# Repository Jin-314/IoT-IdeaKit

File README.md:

# Turtle Pico - Making electronics work easier and more widely

The Turtle Pico Board which looks like a turtle, uses connectors on the board for easy connection to components. The board is equipped with Raspberry Pi Pico W, and programming is easy with Micropython.

When you want to build something, just buy the components and plug them into this board! That's all there is to wiring. Then all you have to do is write the programming.

Don't know how to program? Don't worry. You can find some programming examples in the official repository.

## Specific & Environment build

Please see the specifications for a summary of each use.

The specifications are available in Japanese and English, so you can check them in the language of your choice.

[English](board/main/specific/specific_en.pdf)

[Japanese](board/main/specific/specific_jp.pdf)

## Case

Turtle Pico Package is available in [**board/main/Case**](https://github.com/Jin-Neuron/Turtle-Pico/tree/master/board/main/Case).

## Purchase your board

Turtle Pico boards can currently only be purchased from [PCBWay's Shared Project Page](https://www.pcbway.com/project/shareproject/Turtle_Pico_Board_c183b11f.html). Once officially released, we plan to make it available for purchase at various online stores. 

## License

This repository includes multiple components with different licenses.

Please reffer to [LICENSE File](License.txt).

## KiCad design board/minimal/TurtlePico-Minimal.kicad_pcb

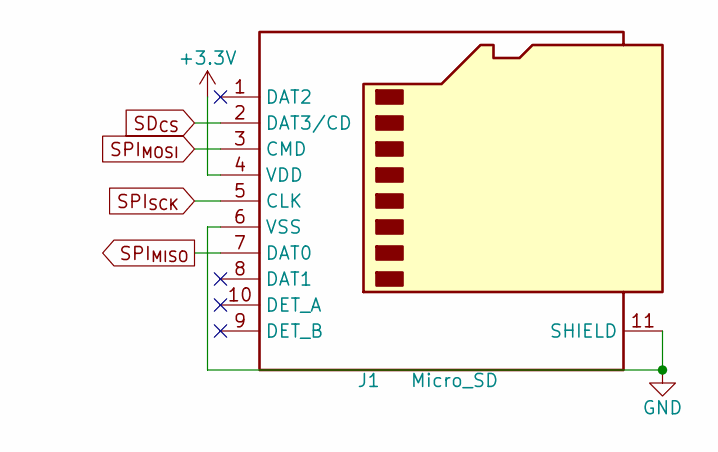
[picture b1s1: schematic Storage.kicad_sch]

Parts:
J1: Micro_SD; microSD_HC_Hirose_DM3D-SF; Manufacturer_Part_Number DM3AT-SF-PEJM5; Mouser Part Number 798-DM3AT-SF-PEJM5

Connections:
+3.3V: J1.4 (VDD); also elsewhere on the board
GND: J1.6 (VSS), J1.11 (SHIELD); also elsewhere on the board
SD_{CS}: J1.2 (DAT3/CD); also elsewhere on the board
SPI_{MISO}: J1.7 (DAT0); also elsewhere on the board
SPI_{MOSI}: J1.3 (CMD); also elsewhere on the board
SPI_{SCK}: J1.5 (CLK); also elsewhere on the board

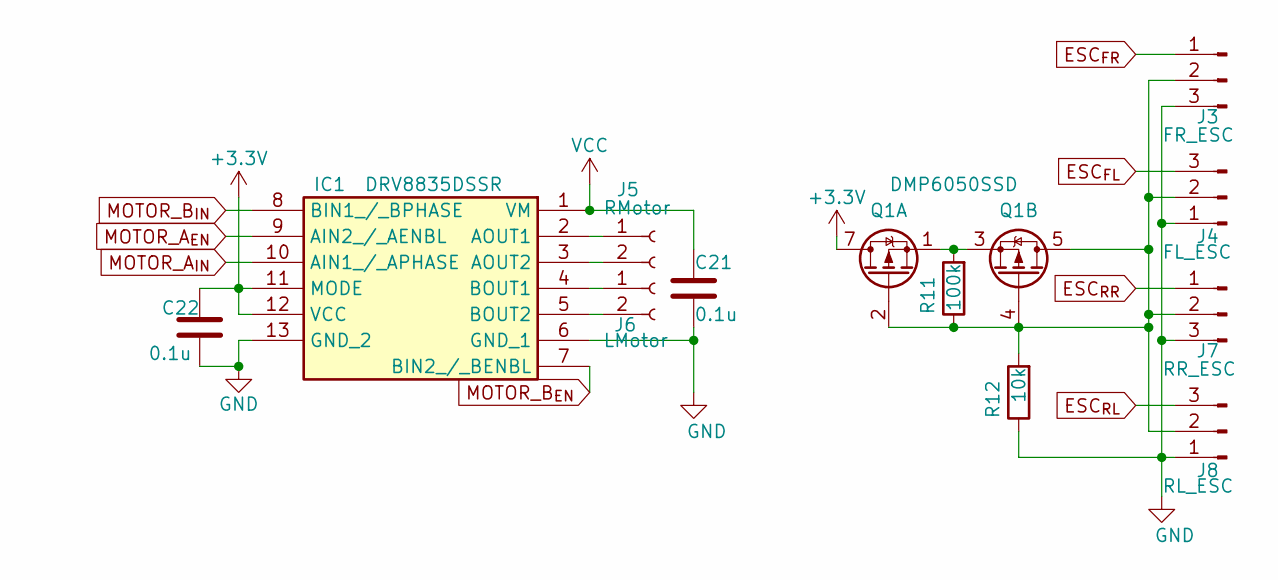
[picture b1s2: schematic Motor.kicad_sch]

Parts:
C21, C22: 0.1u; C_0201_0603Metric; Manufacturer_Part_Number GCM188R71C104KA37J; Mouser Part Number 81-GCM188R71C104KA7J
IC1: DRV8835DSSR; WSON-12-1EP_3x2mm_P0.5mm_EP1x2.65_ThermalVias; Mouser Part Number 595-DRV8835DSSR
J3: FR_ESC; PinHeader_1x03_P2.54mm_Horizontal
J4: FL_ESC; PinHeader_1x03_P2.54mm_Horizontal
J5: RMotor; PinSocket_1x02_P2.54mm_Vertical
J6: LMotor; PinSocket_1x02_P2.54mm_Vertical
J7: RR_ESC; PinHeader_1x03_P2.54mm_Horizontal
J8: RL_ESC; PinHeader_1x03_P2.54mm_Horizontal
Q1: DMP6050SSD; SOIC-8_3.9x4.9mm_P1.27mm
R11: 100k; R_0603_1608Metric; Manufacturer_Part_Number RN73H1JTTD5102F100; Mouser Part Number 660-RN73H1JT5102F100
R12: 10k; R_0603_1608Metric; Manufacturer_Part_Number RN73H1JTTD5102F100; Mouser Part Number 660-RN73H1JT5102F100

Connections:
+3.3V: C22.1, IC1.11 (MODE), IC1.12 (VCC), Q1.7 (D1), Q1.8 (D1); also elsewhere on the board
ESC_{FL}: J4.3; also elsewhere on the board
ESC_{FR}: J3.1; also elsewhere on the board
ESC_{RL}: J8.3; also elsewhere on the board
ESC_{RR}: J7.1; also elsewhere on the board
GND: C21.2, C22.2, IC1.6 (GND_1), IC1.13 (GND_2), J3.3, J4.1, J7.3, J8.1, R12.1; also elsewhere on the board
MOTOR_A_{EN}: IC1.9 (AIN2_/_AENBL); also elsewhere on the board
MOTOR_A_{IN}: IC1.10 (AIN1_/_APHASE); also elsewhere on the board
MOTOR_B_{EN}: IC1.7 (BIN2_/_BENBL); also elsewhere on the board
MOTOR_B_{IN}: IC1.8 (BIN1_/_BPHASE); also elsewhere on the board
unnamed: IC1.2 (AOUT1), J5.1
unnamed: IC1.3 (AOUT2), J5.2
unnamed: IC1.4 (BOUT1), J6.1
unnamed: IC1.5 (BOUT2), J6.2
unnamed: J3.2, J4.2, J7.2, J8.2, Q1.2 (G1), Q1.4 (G2), Q1.5 (D2), Q1.6 (D2), R11.1, R12.2
unnamed: Q1.1 (S1), Q1.3 (S2), R11.2
VCC: C21.1, IC1.1 (VM); also elsewhere on the board

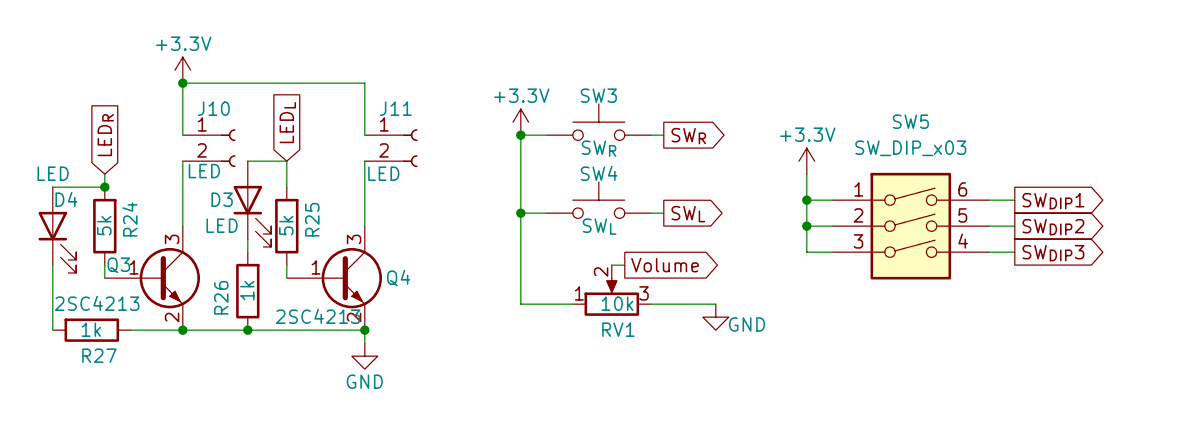
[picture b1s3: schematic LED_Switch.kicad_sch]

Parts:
D3, D4: LED; LED_0603_1608Metric
J10, J11: LED; PinSocket_1x02_P2.54mm_Vertical
Q3, Q4: 2SC4213; SOT-323_SC-70; Manufacturer_Part_Number 2SC4213-A(TE85L,F); Mouser Part Number 757-2SC4213-ATE85LF
R24, R25: 5k; R_0603_1608Metric; Manufacturer_Part_Number RN73H1JTTD5102F100; Mouser Part Number 660-RN73H1JT5102F100
R26, R27: 1k; R_0603_1608Metric; Manufacturer_Part_Number RN73H1JTTD5102F100; Mouser Part Number 660-RN73H1JT5102F100
RV1: 10k; Potentiometer_ACP_CA6-VSMD_Vertical
SW3: SW_{R}; SW_SKRPACE010
SW4: SW_{L}; SW_SKRPACE010
SW5: SW_DIP_x03; DS04254203BKSMT

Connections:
+3.3V: J10.1, J11.1, RV1.1, SW3.1, SW4.1, SW5.1, SW5.2, SW5.3; also elsewhere on the board
GND: Q3.2 (E), Q4.2 (E), R26.1, R27.1, RV1.3; also elsewhere on the board
LED_{L}: D3.2 (A), R25.2; also elsewhere on the board
LED_{R}: D4.2 (A), R24.2; also elsewhere on the board
unnamed: D3.1 (K), R26.2
unnamed: D4.1 (K), R27.2
unnamed: J10.2, Q3.3 (C)
unnamed: J11.2, Q4.3 (C)
unnamed: Q3.1 (B), R24.1
unnamed: Q4.1 (B), R25.1
SW_{DIP}1: SW5.6; also elsewhere on the board
SW_{DIP}2: SW5.5; also elsewhere on the board
SW_{DIP}3: SW5.4; also elsewhere on the board
SW_{L}: SW4.2; also elsewhere on the board
SW_{R}: SW3.2; also elsewhere on the board
Volume: RV1.2; also elsewhere on the board

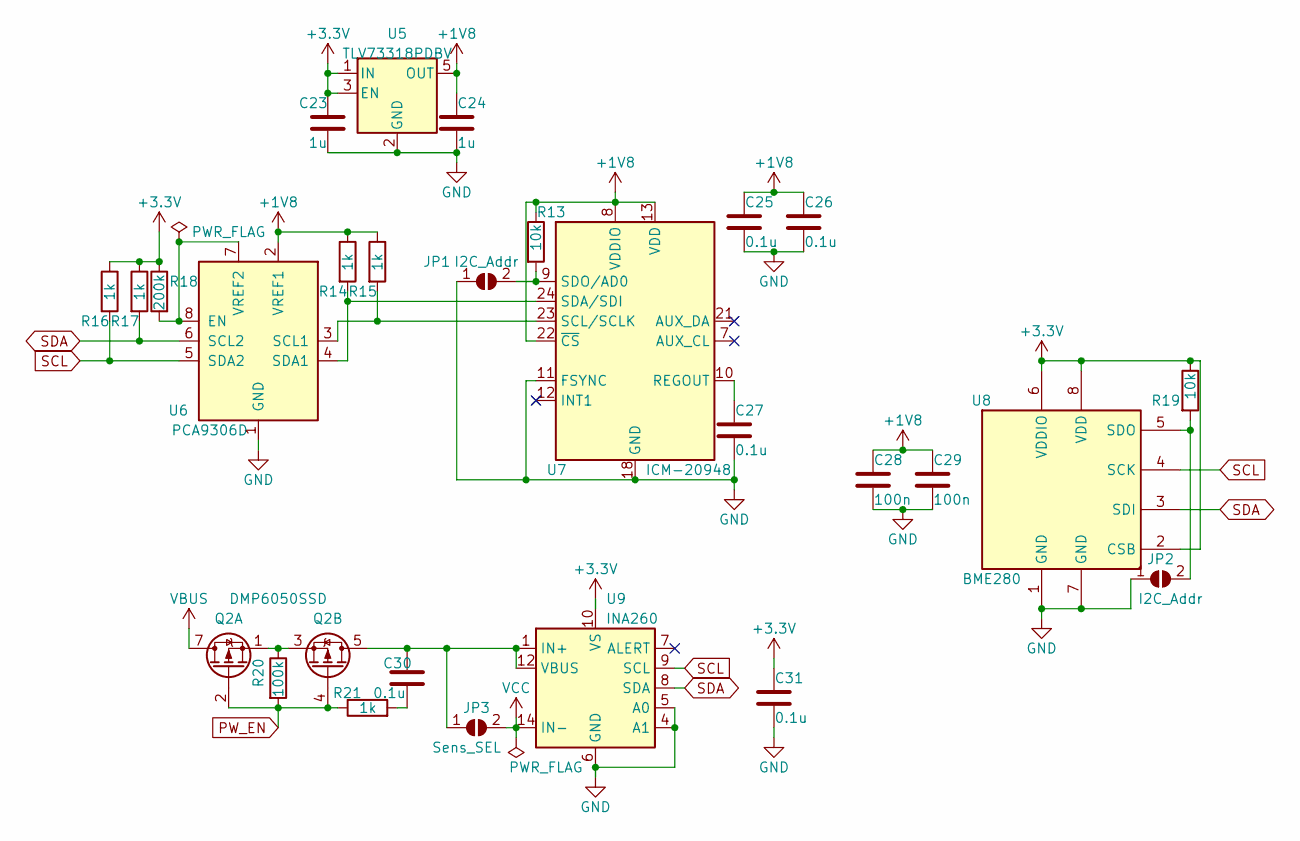
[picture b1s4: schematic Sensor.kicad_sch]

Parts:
C23, C24: 1u; C_0201_0603Metric
C25, C26, C27, C30, C31: 0.1u; C_0201_0603Metric
C28, C29: 100n; C_0201_0603Metric
JP1, JP2: I2C_Addr; SolderJumper-2_P1.3mm_Open_RoundedPad1.0x1.5mm
JP3: Sens_SEL; SolderJumper-2_P1.3mm_Open_RoundedPad1.0x1.5mm
Q2: DMP6050SSD; SOIC-8_3.9x4.9mm_P1.27mm
R13, R19: 10k; R_0603_1608Metric
R14, R15, R16, R17, R21: 1k; R_0603_1608Metric
R18: 200k; R_0603_1608Metric
R20: 100k; R_0603_1608Metric
U5: TLV73318PDBV; SOT-23-5
U6: PCA9306D; X2SON-8_1.4x1mm_P0.35mm
U7: ICM-20948; InvenSense_QFN-24_3x3mm_P0.4mm
U8: BME280; Bosch_LGA-8_2.5x2.5mm_P0.65mm_ClockwisePinNumbering
U9: INA260; TSSOP-16_4.4x5mm_P0.65mm

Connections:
+1V8: C24.1, C25.1, C26.1, C28.1, C29.1, R13.1, R14.1, R15.1, U5.5 (OUT), U6.2 (VREF1), U7.8 (VDDIO), U7.13 (VDD), U7.22 (~CS)
+3.3V: C23.1, C31.1, R16.1, R17.1, R18.1, R19.1, U5.1 (IN), U5.3 (EN), U8.2 (CSB), U8.6 (VDDIO), U8.8 (VDD), U9.10 (VS); also elsewhere on the board
GND: C23.2, C24.2, C25.2, C26.2, C27.2, C28.2, C29.2, C31.2, JP1.1 (A), JP2.1 (A), U5.2 (GND), U6.1 (GND), U7.11 (FSYNC), U7.18 (GND), U7.20 (GND), U8.1 (GND), U8.7 (GND), U9.4 (A1), U9.5 (A0), U9.6 (GND), U9.11 (GND); also elsewhere on the board
unnamed: C30.2, R21.2
unnamed: JP1.2 (B), R13.2, U7.9 (SDO/AD0)
unnamed: JP2.2 (B), R19.2, U8.5 (SDO)
unnamed: C30.1, JP3.1 (A), Q2.5 (D2), Q2.6 (D2), U9.1 (IN+), U9.2 (IN+), U9.3 (IN+), U9.12 (VBUS)
unnamed: Q2.1 (S1), Q2.3 (S2), R20.1
unnamed: R18.2, U6.7 (VREF2), U6.8 (EN)
unnamed: R15.2, U6.3 (SCL1), U7.23 (SCL/SCLK)
unnamed: R14.2, U6.4 (SDA1), U7.24 (SDA/SDI)
unnamed: C27.1, U7.10 (REGOUT)
PW_EN: Q2.2 (G1), Q2.4 (G2), R20.2, R21.1; also elsewhere on the board
SCL: R16.2, U6.5 (SDA2), U8.4 (SCK), U9.9 (SCL); also elsewhere on the board
SDA: R17.2, U6.6 (SCL2), U8.3 (SDI), U9.8 (SDA); also elsewhere on the board
VBUS: Q2.7 (D1), Q2.8 (D1); also elsewhere on the board
VCC: JP3.2 (B), U9.14 (IN-), U9.15 (IN-), U9.16 (IN-); also elsewhere on the board

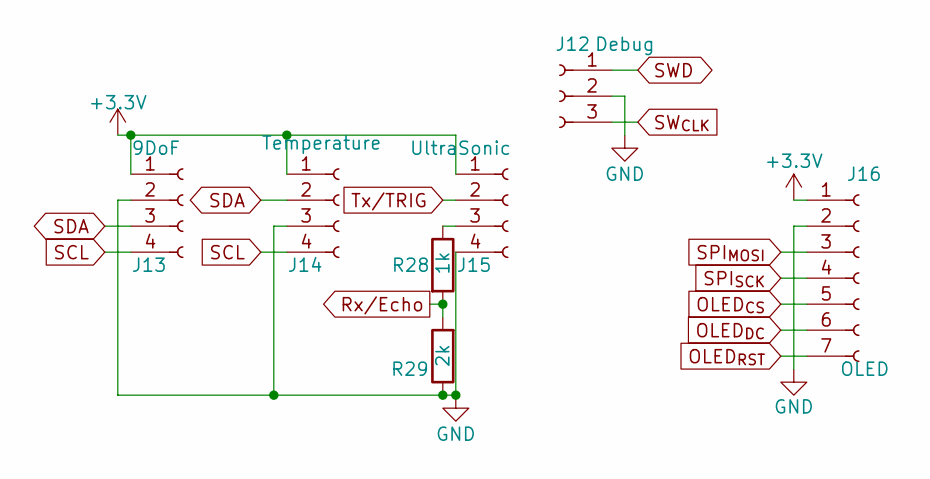
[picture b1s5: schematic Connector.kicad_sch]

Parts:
J12: Debug; JST_PH_B3B-PH-SM4-TB_1x03-1MP_P2.00mm_Vertical
J13: 9DoF; JST_XH_S4B-XH-A_1x04_P2.50mm_Horizontal
J14: Temperature; PinSocket_1x04_P2.54mm_Vertical
J15: UltraSonic; PinSocket_1x04_P2.54mm_Vertical
J16: OLED; JST_XH_S7B-XH-A_1x07_P2.50mm_Horizontal
R28: 1k; R_0603_1608Metric; Manufacturer_Part_Number RN73H1JTTD1001F100; Mouser Part Number 660-RN73H1JT1001F100
R29: 2k; R_0603_1608Metric; Manufacturer_Part_Number RN73H1JTTD2001F25; Mouser Part Number 660-RN73H1JTD2001F25

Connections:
+3.3V: J13.1, J14.1, J15.1, J16.1; also elsewhere on the board
GND: J12.2, J13.2, J14.3, J15.4, J16.2, R29.1; also elsewhere on the board
unnamed: J15.3, R28.1
OLED_{CS}: J16.5; also elsewhere on the board
OLED_{DC}: J16.6; also elsewhere on the board
OLED_{RST}: J16.7; also elsewhere on the board
Rx/Echo: R28.2, R29.2; also elsewhere on the board
SCL: J13.4, J14.4; also elsewhere on the board
SDA: J13.3, J14.2; also elsewhere on the board
SPI_{MOSI}: J16.3; also elsewhere on the board
SPI_{SCK}: J16.4; also elsewhere on the board
SWD: J12.1; also elsewhere on the board
SW_{CLK}: J12.3; also elsewhere on the board
Tx/TRIG: J15.2; also elsewhere on the board

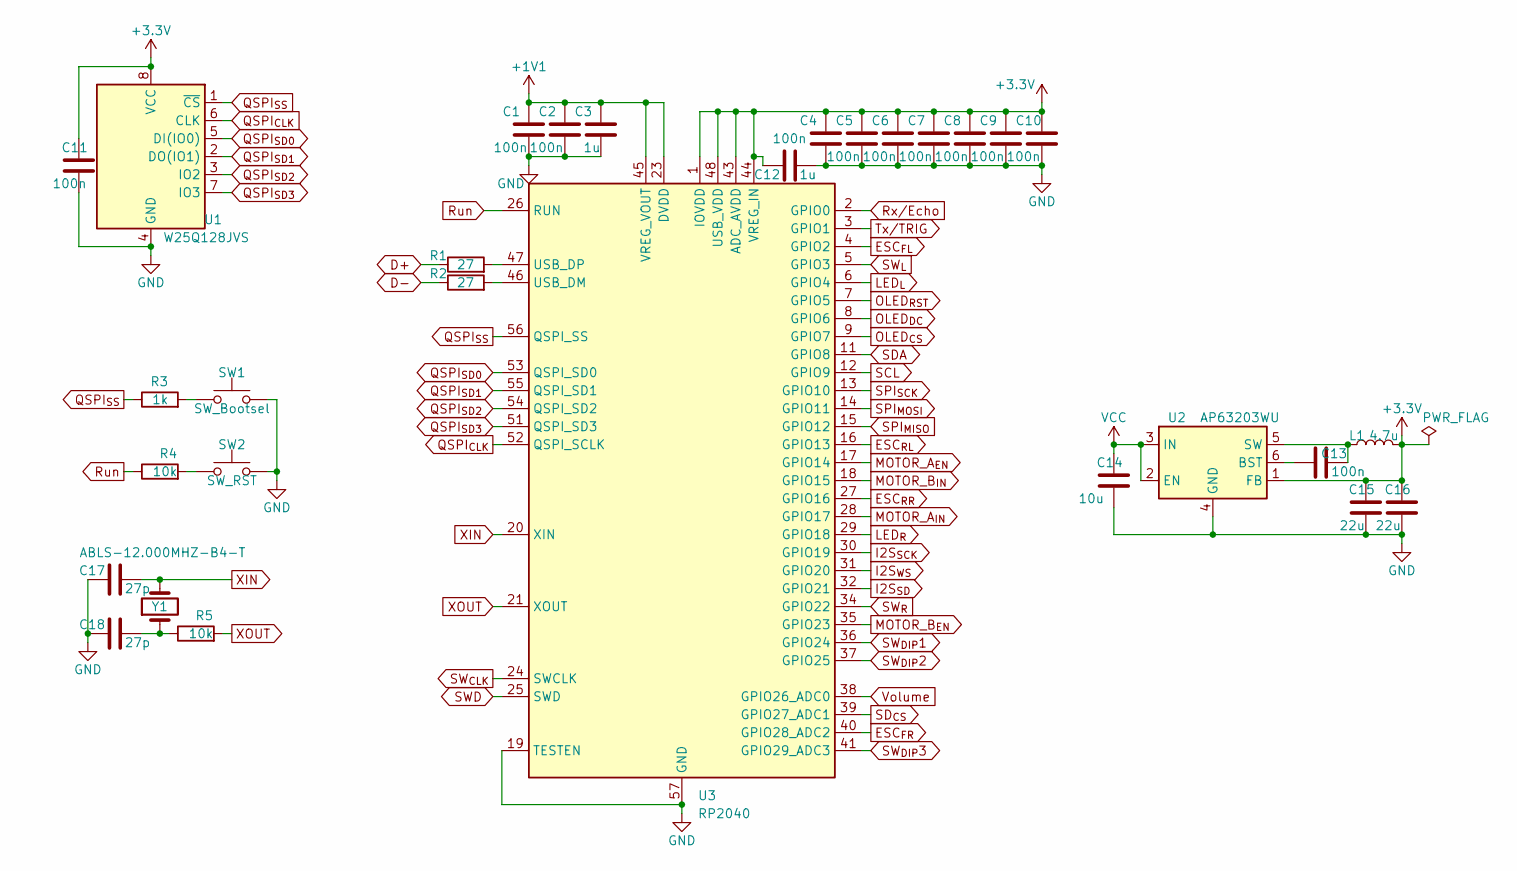
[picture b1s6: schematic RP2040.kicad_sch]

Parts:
C1, C2, C4, C5, C6, C7, C8, C9, C10, C11, C13: 100n; C_0201_0603Metric
C3, C12: 1u; C_0201_0603Metric
C14: 10u; C_1206_3216Metric
C15, C16: 22u; C_0402_1005Metric
C17, C18: 27p; C_0201_0603Metric
L1: 4.7u; C_0603_1608Metric
R1, R2: 27; R_0603_1608Metric
R3: 1k; R_0603_1608Metric
R4, R5: 10k; R_0603_1608Metric
SW1: SW_Bootsel; SW_SKRPACE010
SW2: SW_RST; SW_SKRPACE010
U1: W25Q128JVS; SOIC-8_5.23x5.23mm_P1.27mm
U2: AP63203WU; TSOT-23-6
U3: RP2040; QFN-56-1EP_7x7mm_P0.4mm_EP3.2x3.2mm
Y1: ABLS-12.000MHZ-B4-T; ABLS

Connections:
+1V1: C1.1, C2.1, C3.1, U3.23 (DVDD), U3.45 (VREG_VOUT), U3.50 (DVDD)
+3.3V: C4.1, C5.1, C6.1, C7.1, C8.1, C9.1, C10.1, C11.1, C12.1, C15.1, C16.1, L1.2, U1.8 (VCC), U2.1 (FB), U3.1 (IOVDD), U3.10 (IOVDD), U3.22 (IOVDD), U3.33 (IOVDD), U3.42 (IOVDD), U3.43 (ADC_AVDD), U3.44 (VREG_IN), U3.48 (USB_VDD), U3.49 (IOVDD); also elsewhere on the board
D+: R1.1; also elsewhere on the board
D-: R2.1; also elsewhere on the board
ESC_{FL}: U3.4 (GPIO2); also elsewhere on the board
ESC_{FR}: U3.40 (GPIO28_ADC2); also elsewhere on the board
ESC_{RL}: U3.16 (GPIO13); also elsewhere on the board
ESC_{RR}: U3.27 (GPIO16); also elsewhere on the board
GND: C1.2, C2.2, C3.2, C4.2, C5.2, C6.2, C7.2, C8.2, C9.2, C10.2, C11.2, C12.2, C14.2, C15.2, C16.2, C17.1, C18.1, SW1.2, SW2.2, U1.4 (GND), U2.4 (GND), U3.19 (TESTEN), U3.57 (GND); also elsewhere on the board
I2S_{SCK}: U3.30 (GPIO19); also elsewhere on the board
I2S_{SD}: U3.32 (GPIO21); also elsewhere on the board
I2S_{WS}: U3.31 (GPIO20); also elsewhere on the board
LED_{L}: U3.6 (GPIO4); also elsewhere on the board
LED_{R}: U3.29 (GPIO18); also elsewhere on the board
MOTOR_A_{EN}: U3.17 (GPIO14); also elsewhere on the board
MOTOR_A_{IN}: U3.28 (GPIO17); also elsewhere on the board
MOTOR_B_{EN}: U3.35 (GPIO23); also elsewhere on the board
MOTOR_B_{IN}: U3.18 (GPIO15); also elsewhere on the board
unnamed: C18.2, R5.1, Y1.1
unnamed: R3.2, SW1.1
unnamed: R4.2, SW2.1
unnamed: C13.1, U2.6 (BST)
unnamed: C13.2, L1.1, U2.5 (SW)
unnamed: R2.2, U3.46 (USB_DM)
unnamed: R1.2, U3.47 (USB_DP)
OLED_{CS}: U3.9 (GPIO7); also elsewhere on the board
OLED_{DC}: U3.8 (GPIO6); also elsewhere on the board
OLED_{RST}: U3.7 (GPIO5); also elsewhere on the board
QSPI_{CLK}: U1.6 (CLK), U3.52 (QSPI_SCLK)
QSPI_{SD0}: U1.5 (DI(IO0)), U3.53 (QSPI_SD0)
QSPI_{SD1}: U1.2 (DO(IO1)), U3.55 (QSPI_SD1)
QSPI_{SD2}: U1.3 (IO2), U3.54 (QSPI_SD2)
QSPI_{SD3}: U1.7 (IO3), U3.51 (QSPI_SD3)
QSPI_{SS}: R3.1, U1.1 (~CS), U3.56 (QSPI_SS)
Run: R4.1, U3.26 (RUN)
Rx/Echo: U3.2 (GPIO0); also elsewhere on the board
SCL: U3.12 (GPIO9); also elsewhere on the board
SDA: U3.11 (GPIO8); also elsewhere on the board
SD_{CS}: U3.39 (GPIO27_ADC1); also elsewhere on the board
SPI_{MISO}: U3.15 (GPIO12); also elsewhere on the board
SPI_{MOSI}: U3.14 (GPIO11); also elsewhere on the board
SPI_{SCK}: U3.13 (GPIO10); also elsewhere on the board
SWD: U3.25 (SWD); also elsewhere on the board
SW_{CLK}: U3.24 (SWCLK); also elsewhere on the board
SW_{DIP}1: U3.36 (GPIO24); also elsewhere on the board
SW_{DIP}2: U3.37 (GPIO25); also elsewhere on the board
SW_{DIP}3: U3.41 (GPIO29_ADC3); also elsewhere on the board
SW_{L}: U3.5 (GPIO3); also elsewhere on the board
SW_{R}: U3.34 (GPIO22); also elsewhere on the board
Tx/TRIG: U3.3 (GPIO1); also elsewhere on the board
VCC: C14.1, U2.2 (EN), U2.3 (IN); also elsewhere on the board
Volume: U3.38 (GPIO26_ADC0); also elsewhere on the board
XIN: C17.2, U3.20 (XIN), Y1.2
XOUT: R5.2, U3.21 (XOUT)

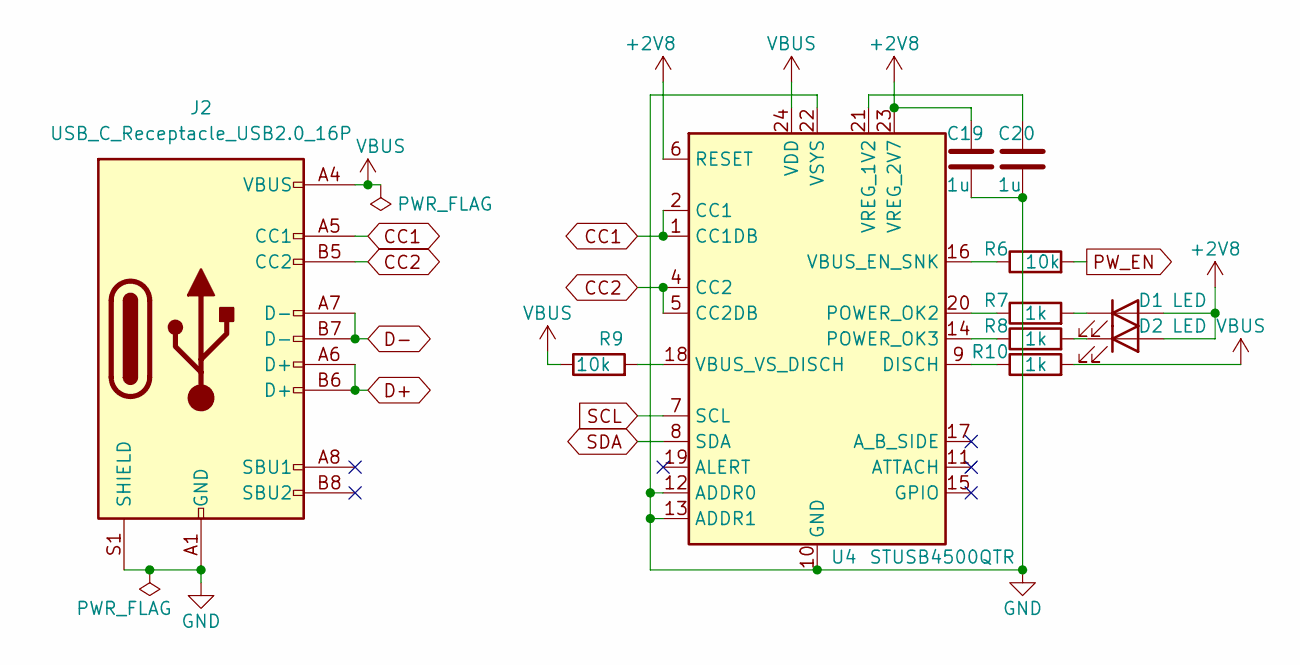
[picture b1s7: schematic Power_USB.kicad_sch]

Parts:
C19, C20: 1u; C_0201_0603Metric
D1, D2: LED; LED_0603_1608Metric
J2: USB_C_Receptacle_USB2.0_16P; USB_C_Receptacle_GCT_USB4085
R6, R9: 10k; R_0603_1608Metric
R7, R8, R10: 1k; R_0603_1608Metric
U4: STUSB4500QTR; QFN-24-1EP_4x4mm_P0.5mm_EP2.7x2.7mm

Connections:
+2V8: C19.1, D1.2 (A), D2.2 (A), U4.6 (RESET), U4.23 (VREG_2V7)
CC1: J2.A5 (CC1), U4.1 (CC1DB), U4.2 (CC1)
CC2: J2.B5 (CC2), U4.4 (CC2), U4.5 (CC2DB)
D+: J2.A6 (D+), J2.B6 (D+); also elsewhere on the board
D-: J2.A7 (D-), J2.B7 (D-); also elsewhere on the board
GND: C19.2, C20.2, J2.A1 (GND), J2.A12 (GND), J2.B1 (GND), J2.B12 (GND), J2.S1 (SHIELD), U4.10 (GND), U4.12 (ADDR0), U4.13 (ADDR1), U4.22 (VSYS), U4.25 (GND); also elsewhere on the board
unnamed: D1.1 (K), R7.2
unnamed: D2.1 (K), R8.2
unnamed: R10.1, U4.9 (DISCH)
unnamed: R7.1, U4.20 (POWER_OK2)
unnamed: R8.1, U4.14 (POWER_OK3)
unnamed: R6.1, U4.16 (VBUS_EN_SNK)
unnamed: R9.2, U4.18 (VBUS_VS_DISCH)
unnamed: C20.1, U4.21 (VREG_1V2)
PW_EN: R6.2; also elsewhere on the board
SCL: U4.7 (SCL); also elsewhere on the board
SDA: U4.8 (SDA); also elsewhere on the board
VBUS: J2.A4 (VBUS), J2.A9 (VBUS), J2.B4 (VBUS), J2.B9 (VBUS), R9.1, R10.2, U4.24 (VDD); also elsewhere on the board

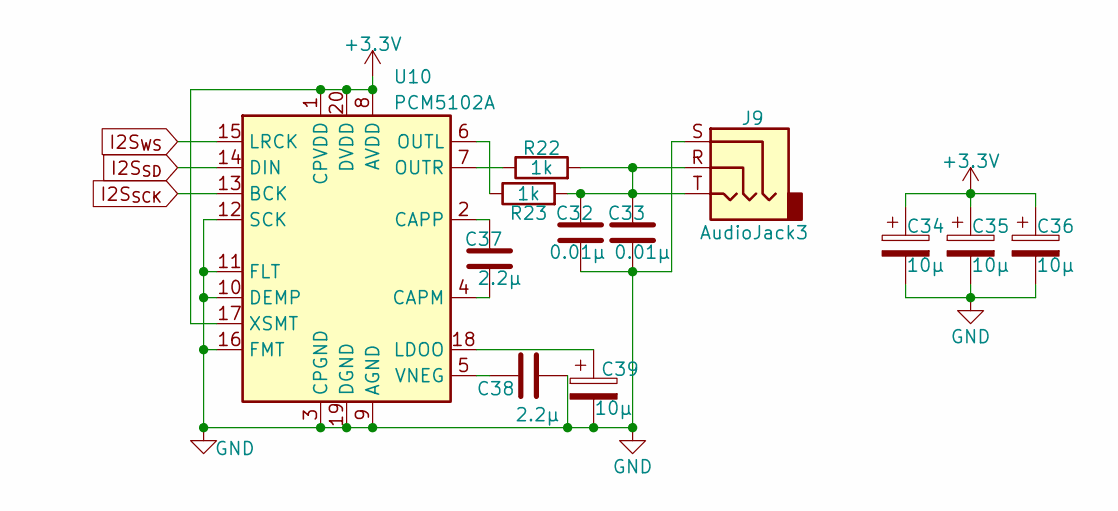
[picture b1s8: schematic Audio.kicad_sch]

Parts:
C32, C33: 0.01µ; C_0201_0603Metric; Manufacturer_Part_Number GCM188R71H103KA37J; Mouser Part Number 81-GCM188R71H103KA7J
C34, C35, C36, C39: 10µ; CP_Elec_4x5.4; Manufacturer_Part_Number EEE-FN1A100R; Mouser Part Number 667-EEE-FN1A100R
C37, C38: 2.2µ; C_0201_0603Metric; Manufacturer_Part_Number GRM188R61H225KE11D; Mouser Part Number 81-GRM188R61H225KE1D
J9: AudioJack3; STX3000; Manufacturer_Part_Number STX-3000; Mouser Part Number 806-STX-3000
R22, R23: 1k; R_0603_1608Metric; Manufacturer_Part_Number RN73H1JTTD1001F100; Mouser Part Number 660-RN73H1JT1001F100
U10: PCM5102A; TSSOP-20_4.4x6.5mm_P0.65mm; Manufacturer_Part_Number PCM5102APWR; Mouser Part Number 595-PCM5102APWR

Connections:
+3.3V: C34.1, C35.1, C36.1, U10.1 (CPVDD), U10.8 (AVDD), U10.17 (XSMT), U10.20 (DVDD); also elsewhere on the board
GND: C32.2, C33.2, C34.2, C35.2, C36.2, C38.2, C39.2, J9.S, U10.3 (CPGND), U10.9 (AGND), U10.10 (DEMP), U10.11 (FLT), U10.12 (SCK), U10.16 (FMT), U10.19 (DGND); also elsewhere on the board
I2S_{SCK}: U10.13 (BCK); also elsewhere on the board
I2S_{SD}: U10.14 (DIN); also elsewhere on the board
I2S_{WS}: U10.15 (LRCK); also elsewhere on the board
unnamed: C32.1, C33.1, J9.R, J9.T, R22.2, R23.2
unnamed: C37.2, U10.4 (CAPM)
unnamed: C37.1, U10.2 (CAPP)
unnamed: C39.1, U10.18 (LDOO)
unnamed: R23.1, U10.6 (OUTL)
unnamed: R22.1, U10.7 (OUTR)
unnamed: C38.1, U10.5 (VNEG)

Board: 2 copper layers, 114 parts (8 on the bottom side), 97 nets, no tracks yet.

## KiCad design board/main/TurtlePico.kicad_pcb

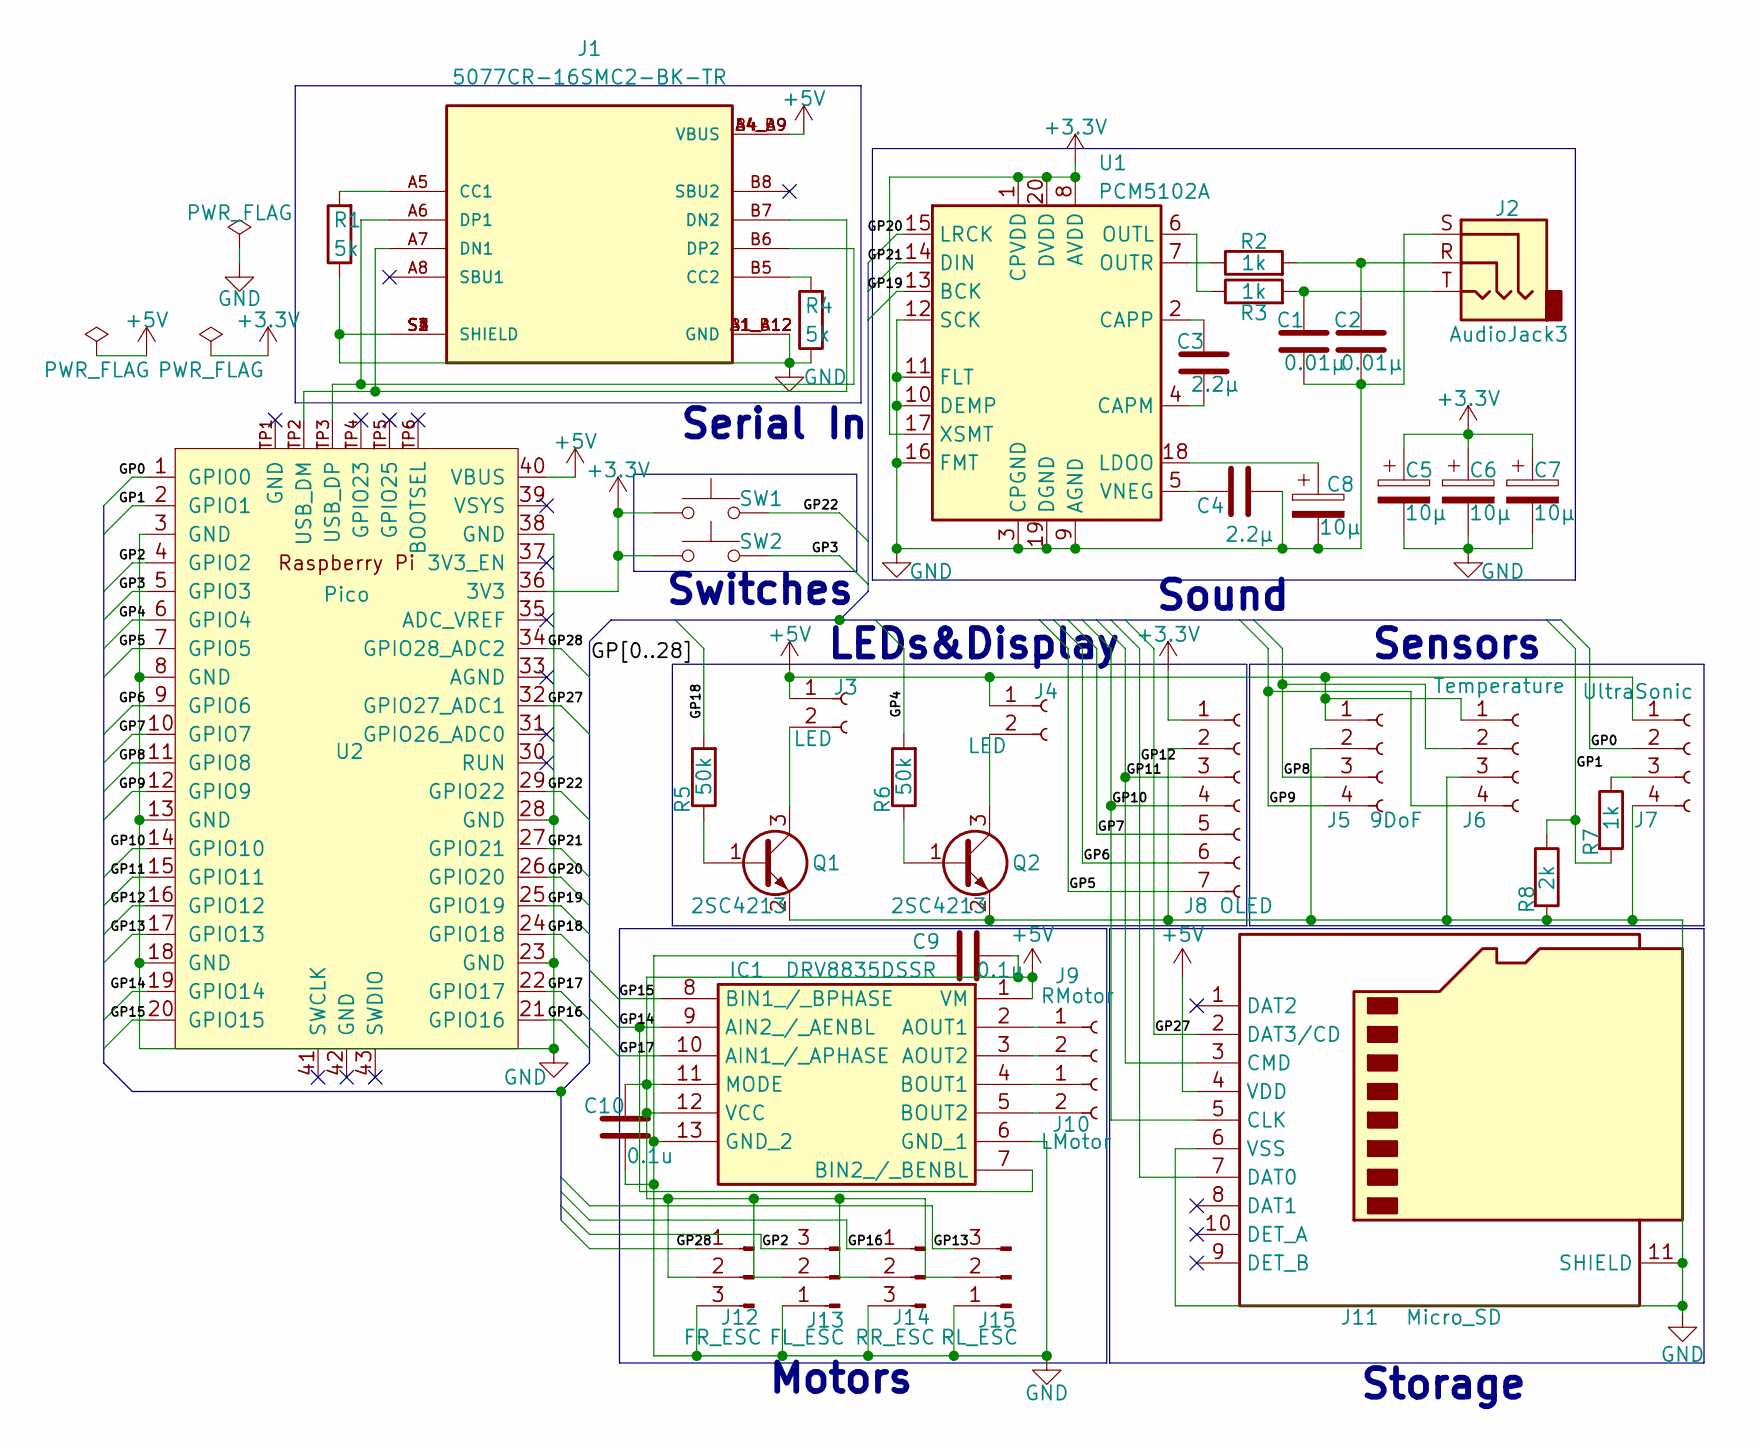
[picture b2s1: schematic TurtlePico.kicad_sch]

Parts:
C1, C2: 0.01µ; C_0603_1608Metric; Manufacturer_Part_Number GCM188R71H103KA37J; Mouser Part Number 81-GCM188R71H103KA7J
C3, C4: 2.2µ; C_0603_1608Metric; Manufacturer_Part_Number GRM188R61H225KE11D; Mouser Part Number 81-GRM188R61H225KE1D
C5, C6, C7, C8: 10µ; CP_Elec_4x5.4; Manufacturer_Part_Number EEE-FN1A100R; Mouser Part Number 667-EEE-FN1A100R
C9, C10: 0.1u; C_0603_1608Metric; Manufacturer_Part_Number GCM188R71C104KA37J; Mouser Part Number 81-GCM188R71C104KA7J
IC1: DRV8835DSSR; Mouser Part Number 595-DRV8835DSSR
J1: 5077CR-16SMC2-BK-TR; NELTRON_5077CR-16SMC2-BK-TR; Manufacturer_Part_Number USB4105-GF-A-060; Mouser Part Number 640-USB4105-GF-A-060
J2: AudioJack3; STX3000; Manufacturer_Part_Number STX-3000; Mouser Part Number 806-STX-3000
J3, J4: LED; PinSocket_1x02_P2.54mm_Vertical
J5: 9DoF; JST_XH_S4B-XH-A_1x04_P2.50mm_Horizontal
J6: Temperature; PinSocket_1x04_P2.54mm_Vertical
J7: UltraSonic; PinSocket_1x04_P2.54mm_Vertical
J8: OLED; JST_XH_S7B-XH-A_1x07_P2.50mm_Horizontal
J9: RMotor; PinSocket_1x02_P2.54mm_Vertical
J10: LMotor; PinSocket_1x02_P2.54mm_Vertical
J11: Micro_SD; microSD_HC_Hirose_DM3AT-SF-PEJM5; Manufacturer_Part_Number DM3AT-SF-PEJM5; Mouser Part Number 798-DM3AT-SF-PEJM5
J12: FR_ESC; PinHeader_1x03_P2.54mm_Horizontal
J13: FL_ESC; PinHeader_1x03_P2.54mm_Horizontal
J14: RR_ESC; PinHeader_1x03_P2.54mm_Horizontal
J15: RL_ESC; PinHeader_1x03_P2.54mm_Horizontal
Q1, Q2: 2SC4213; SOT-323_SC-70; Manufacturer_Part_Number 2SC4213-A(TE85L,F); Mouser Part Number 757-2SC4213-ATE85LF
R1, R4: 5k; R_0603_1608Metric; Manufacturer_Part_Number RN73H1JTTD5101D100; Mouser Part Number 660-RN73H1JT5101D100
R2, R3, R7: 1k; R_0603_1608Metric; Manufacturer_Part_Number RN73H1JTTD1001F100; Mouser Part Number 660-RN73H1JT1001F100
R5, R6: 50k; R_0603_1608Metric; Manufacturer_Part_Number RN73H1JTTD5102F100; Mouser Part Number 660-RN73H1JT5102F100
R8: 2k; R_0603_1608Metric; Manufacturer_Part_Number RN73H1JTTD2001F25; Mouser Part Number 660-RN73H1JTD2001F25
SW1, SW2: SW_Push; SW_SKRPACE010; Manufacturer_Part_Number SKRPACE010; Mouser Part Number 688-SKRPACE010
U1: PCM5102A; TSSOP-20_4.4x6.5mm_P0.65mm; Manufacturer_Part_Number PCM5102APWR; Mouser Part Number 595-PCM5102APWR
U2: Pico; RPi_Pico_SMD_TH; Manufacturer_Part_Number SC0918; Mouser Part Number 358-SC0918

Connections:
+3.3V: C5.1, C6.1, C7.1, J8.1, SW1.1, SW2.1, U1.1 (CPVDD), U1.8 (AVDD), U1.17 (XSMT), U1.20 (DVDD), U2.36 (3V3)
+5V: C9.1, C10.1, IC1.1 (VM), IC1.11 (MODE), IC1.12 (VCC), J1.A4_B9 (VBUS), J1.B4_A9 (VBUS), J3.1, J4.1, J5.1, J6.1, J7.1, J11.4 (VDD), J12.2, J13.2, J14.2, J15.2, U2.40 (VBUS)
/GP0: J7.2, U2.1 (GPIO0)
/GP1: R7.2, R8.1, U2.2 (GPIO1)
/GP2: J13.3, U2.4 (GPIO2)
/GP3: SW2.2, U2.5 (GPIO3)
/GP4: R6.2, U2.6 (GPIO4)
/GP5: J8.7, U2.7 (GPIO5)
/GP6: J8.6, U2.9 (GPIO6)
/GP7: J8.5, U2.10 (GPIO7)
/GP8: J5.3, J6.2, U2.11 (GPIO8)
/GP9: J5.4, J6.4, U2.12 (GPIO9)
/GP10: J8.4, J11.5 (CLK), U2.14 (GPIO10)
/GP11: J8.3, J11.3 (CMD), U2.15 (GPIO11)
/GP12: J11.7 (DAT0), U2.16 (GPIO12)
/GP13: J15.3, U2.17 (GPIO13)
/GP14: IC1.7 (BIN2_/_BENBL), IC1.9 (AIN2_/_AENBL), U2.19 (GPIO14)
/GP15: IC1.8 (BIN1_/_BPHASE), U2.20 (GPIO15)
/GP16: J14.1, U2.21 (GPIO16)
/GP17: IC1.10 (AIN1_/_APHASE), U2.22 (GPIO17)
/GP18: R5.2, U2.24 (GPIO18)
/GP19: U1.13 (BCK), U2.25 (GPIO19)
/GP20: U1.15 (LRCK), U2.26 (GPIO20)
/GP21: U1.14 (DIN), U2.27 (GPIO21)
/GP22: SW1.2, U2.29 (GPIO22)
/GP27: J11.2 (DAT3/CD), U2.32 (GPIO27_ADC1)
/GP28: J12.1, U2.34 (GPIO28_ADC2)
GND: C1.2, C2.2, C4.2, C5.2, C6.2, C7.2, C8.2, C9.2, C10.2, IC1.6 (GND_1), IC1.13 (GND_2), J1.A1_B12 (GND), J1.B1_A12 (GND), J1.S1 (SHIELD), J1.S2 (SHIELD), J1.S3 (SHIELD), J1.S4 (SHIELD), J2.S, J5.2, J6.3, J7.4, J8.2, J11.6 (VSS), J11.11 (SHIELD), J12.3, J13.1, J14.3, J15.1, Q1.2 (E), Q2.2 (E), R1.1, R4.1, R8.2, U1.3 (CPGND), U1.9 (AGND), U1.10 (DEMP), U1.11 (FLT), U1.12 (SCK), U1.16 (FMT), U1.19 (DGND), U2.3 (GND), U2.8 (GND), U2.13 (GND), U2.18 (GND), U2.23 (GND), U2.28 (GND), U2.38 (GND)
unnamed: C1.1, J2.T, R3.2
unnamed: C2.1, J2.R, R2.2
unnamed: IC1.2 (AOUT1), J9.1
unnamed: IC1.3 (AOUT2), J9.2
unnamed: IC1.4 (BOUT1), J10.1
unnamed: IC1.5 (BOUT2), J10.2
unnamed: J1.A5 (CC1), R1.2
unnamed: J1.B5 (CC2), R4.2
unnamed: J1.A7 (DN1), J1.B7 (DN2), U2.TP2 (USB_DM)
unnamed: J1.A6 (DP1), J1.B6 (DP2), U2.TP3 (USB_DP)
unnamed: J3.2, Q1.3 (C)
unnamed: J4.2, Q2.3 (C)
unnamed: J7.3, R7.1
unnamed: Q1.1 (B), R5.1
unnamed: Q2.1 (B), R6.1
unnamed: C3.2, U1.4 (CAPM)
unnamed: C3.1, U1.2 (CAPP)
unnamed: C8.1, U1.18 (LDOO)
unnamed: R3.1, U1.6 (OUTL)
unnamed: R2.1, U1.7 (OUTR)
unnamed: C4.1, U1.5 (VNEG)

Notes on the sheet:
Sensors
LEDs&Display
Serial In
Switches
Motors
Sound
Storage

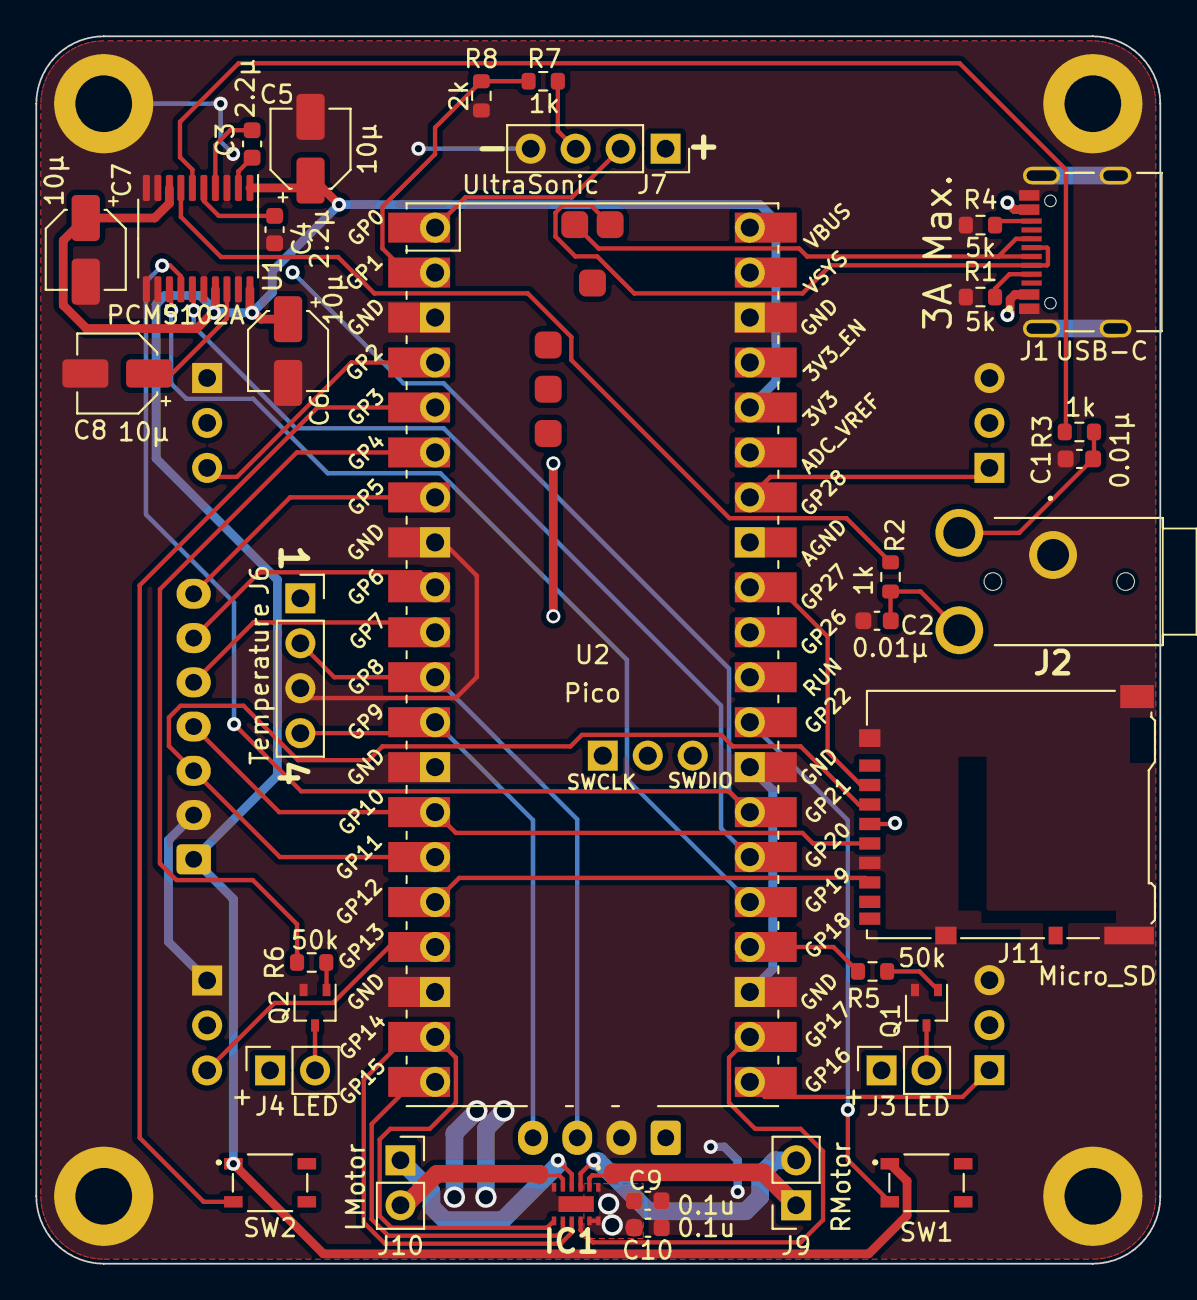
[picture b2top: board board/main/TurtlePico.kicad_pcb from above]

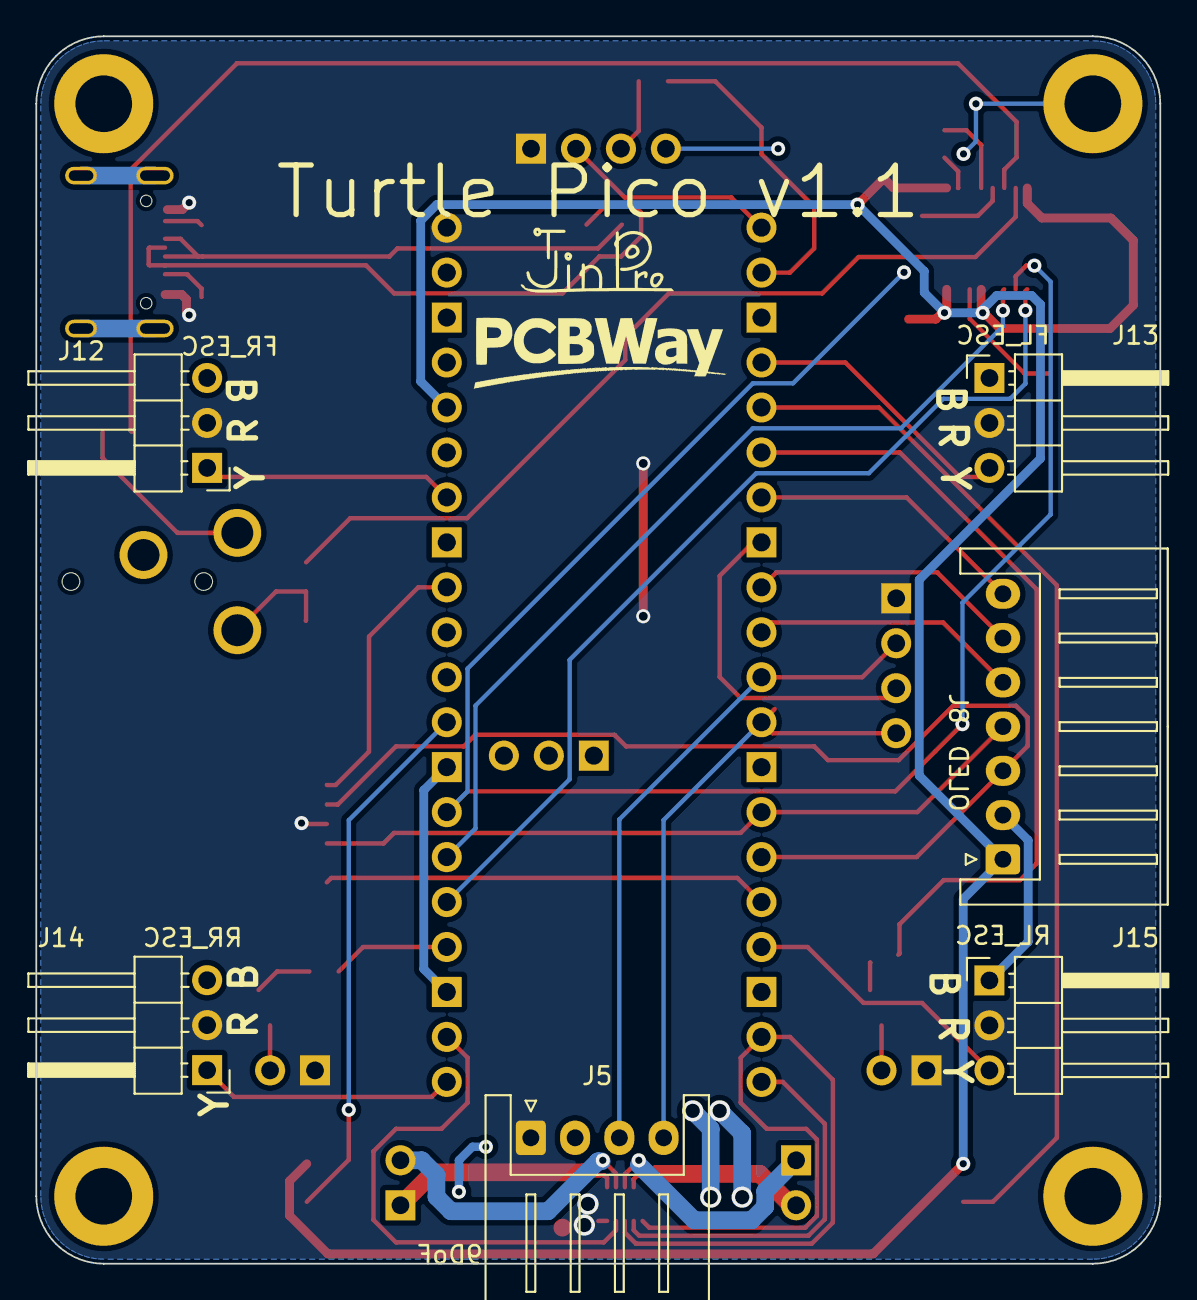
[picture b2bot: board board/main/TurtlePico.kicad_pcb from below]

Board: 2 copper layers, 63.5 x 69.3 mm, 40 parts (6 on the bottom side), 49 nets.
